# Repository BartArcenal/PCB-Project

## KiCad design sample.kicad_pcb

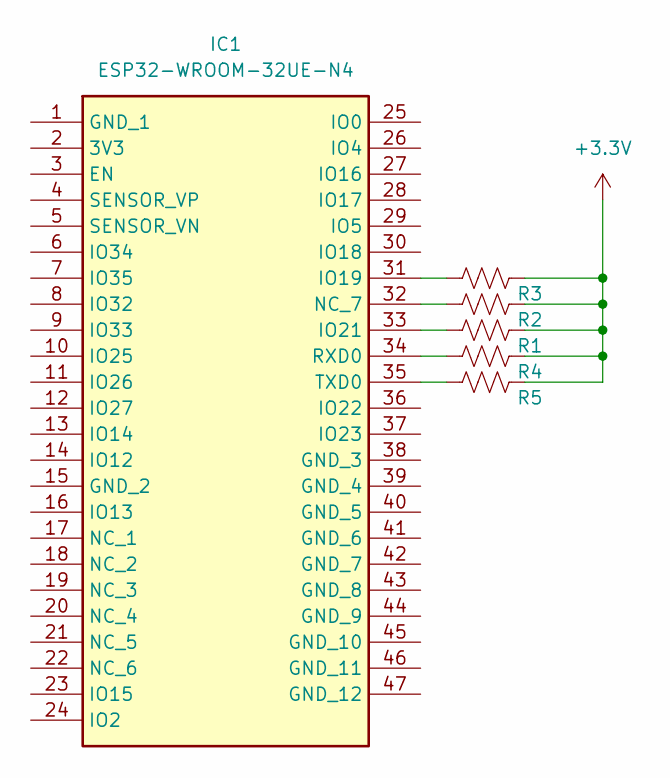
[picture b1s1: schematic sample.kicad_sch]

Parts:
IC1: ESP32-WROOM-32UE-N4; ESP32-WROOM-32D; Manufacturer_Part_Number ESP32-WROOM-32UE-N4; Mouser Part Number 356-ESP32WRM32UE32UH
R1, R2, R3, R4, R5: R_US; R_0603_1608Metric

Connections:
+3.3V: R1.2, R2.2, R3.2, R4.2, R5.2
unnamed: IC1.31 (IO19), R3.1
unnamed: IC1.33 (IO21), R1.1
unnamed: IC1.32 (NC_7), R2.1
unnamed: IC1.34 (RXD0), R4.1
unnamed: IC1.35 (TXD0), R5.1

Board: 2 copper layers, 6 parts (0 on the bottom side), 6 nets, no tracks yet.

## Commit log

2025-12-09 Add files via upload
    version1
